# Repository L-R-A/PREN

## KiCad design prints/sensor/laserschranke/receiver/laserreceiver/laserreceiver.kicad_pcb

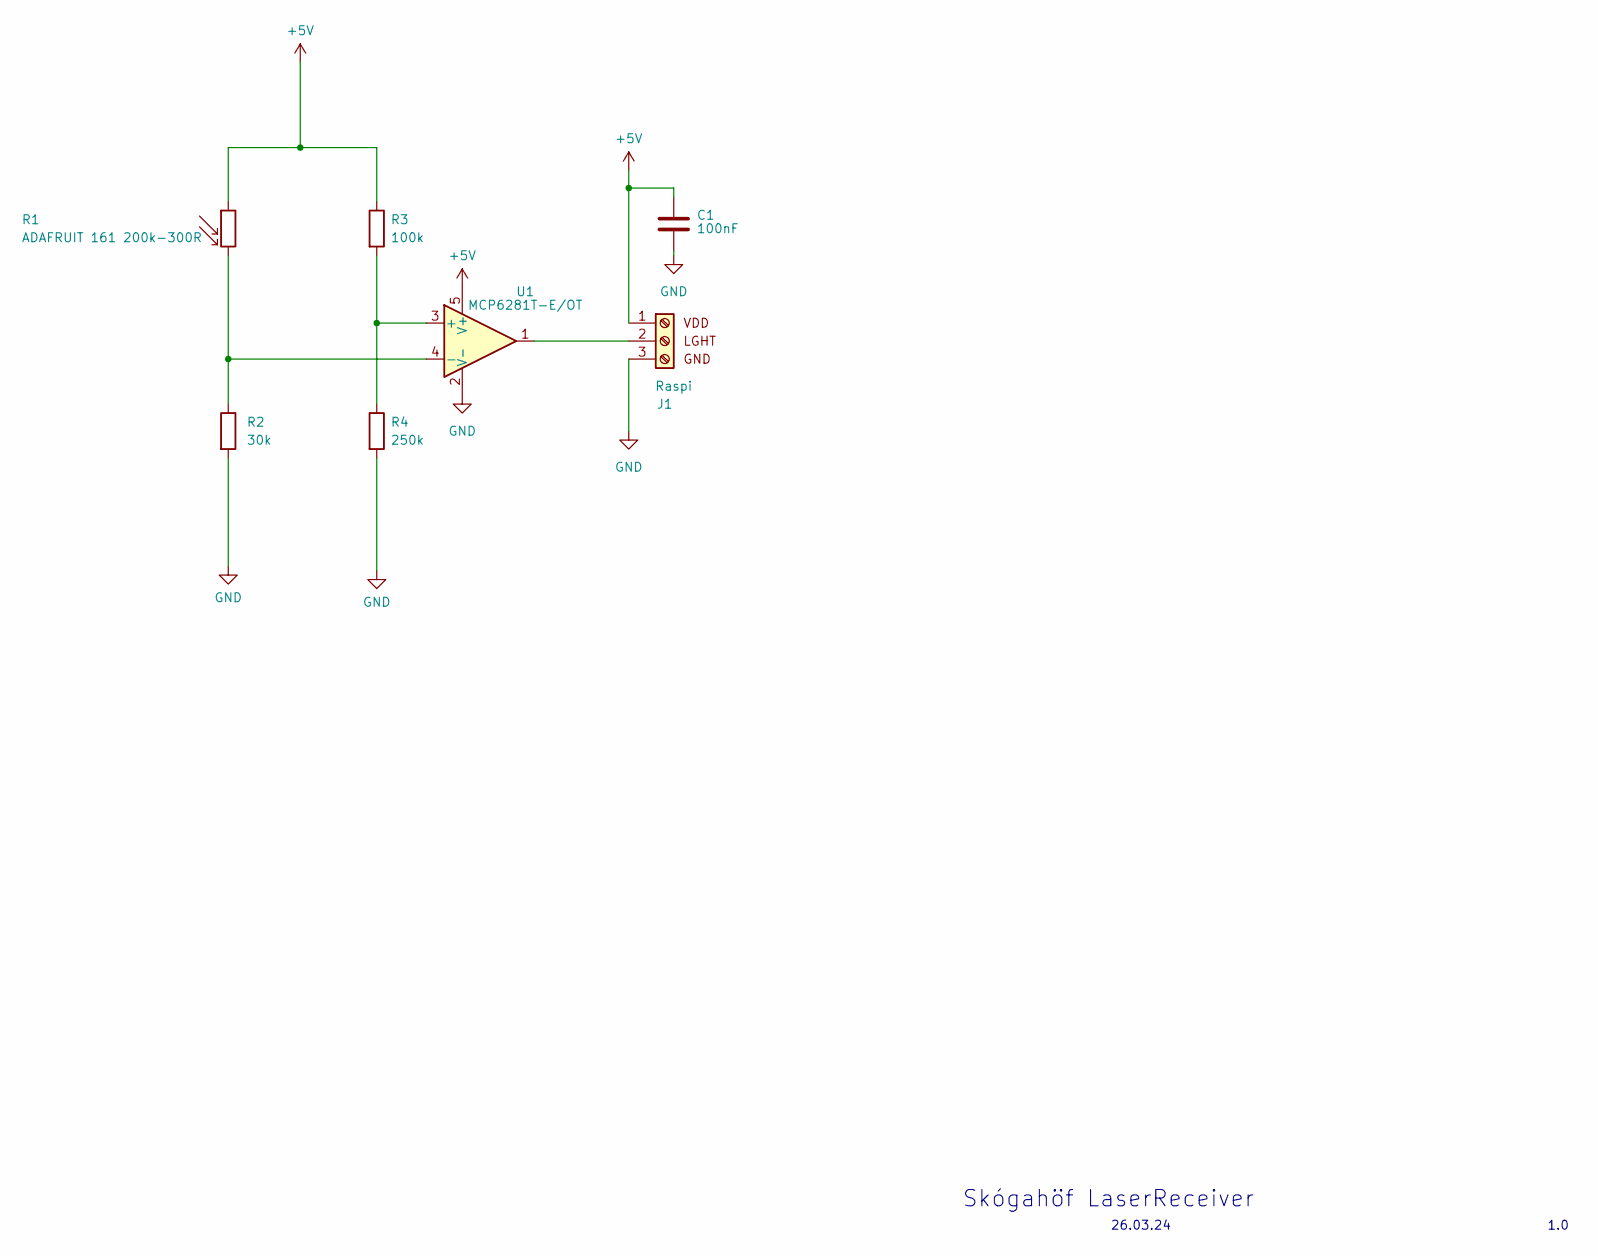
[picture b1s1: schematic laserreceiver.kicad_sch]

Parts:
C1: 100nF; C_0805_2012Metric_Pad1.18x1.45mm_HandSolder
J1: Raspi; TerminalBlock_4Ucon_1x03_P3.50mm_Vertical
R1: ADAFRUIT 161 200k-300R; XDCR_161
R2: 30k; R_0805_2012Metric_Pad1.20x1.40mm_HandSolder
R3: 100k; R_0805_2012Metric_Pad1.20x1.40mm_HandSolder
R4: 250k; R_0805_2012Metric_Pad1.20x1.40mm_HandSolder
U1: MCP6281T-E/OT; SOT-23-5

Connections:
+5V: C1.1, J1.1, R1.1, R3.1, U1.5 (V+)
GND: C1.2, J1.3, R2.2, R4.2, U1.2 (V-)
unnamed: J1.2, U1.1
unnamed: R3.2, R4.1, U1.3 (+)
unnamed: R1.2, R2.1, U1.4 (-)

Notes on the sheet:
1.0
26.03.24
Skógahöf LaserReceiver

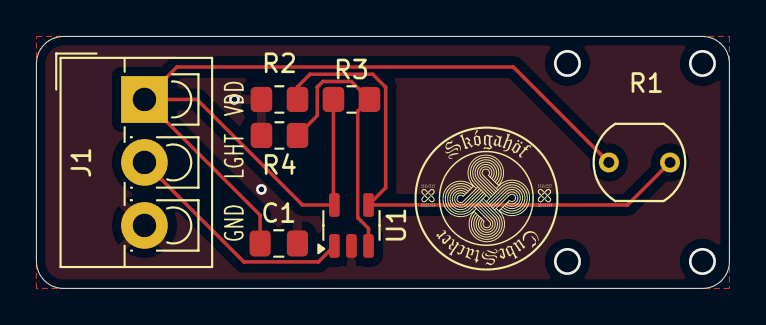
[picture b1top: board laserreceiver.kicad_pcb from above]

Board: 2 copper layers, 38.5 x 14.0 mm, 7 parts (0 on the bottom side), 5 nets.

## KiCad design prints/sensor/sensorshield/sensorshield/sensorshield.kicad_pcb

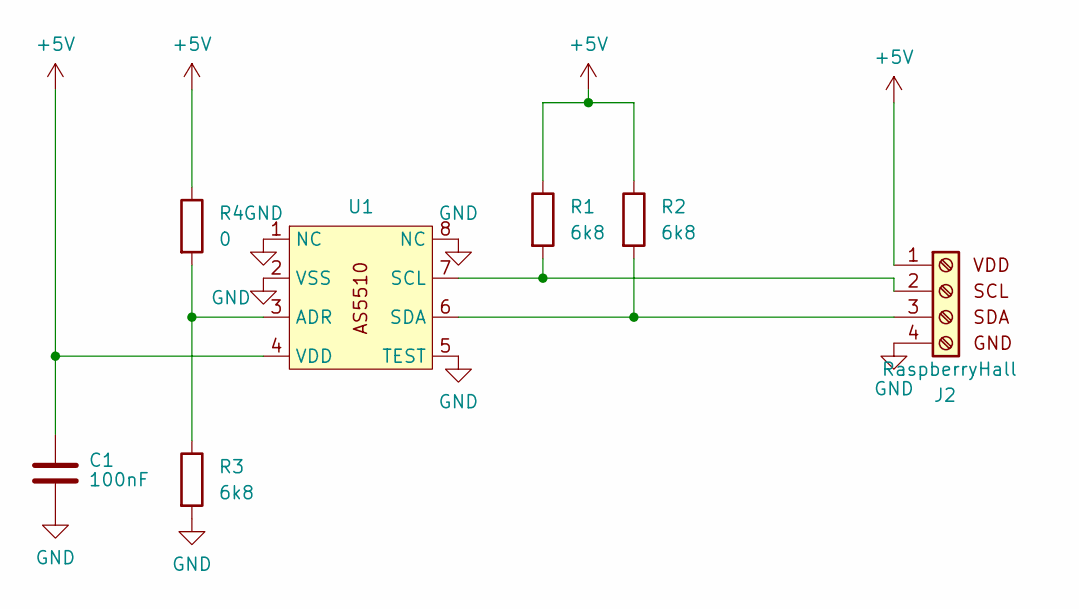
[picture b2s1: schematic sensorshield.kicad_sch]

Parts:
C1: 100nF; C_0805_2012Metric_Pad1.18x1.45mm_HandSolder
J2: RaspberryHall; TerminalBlock_4Ucon_1x04_P3.50mm_Vertical
R1, R2, R3: 6k8; R_0805_2012Metric_Pad1.20x1.40mm_HandSolder
R4: 0; R_0805_2012Metric_Pad1.20x1.40mm_HandSolder
U1: SOIC-8_3.9x4.9mm_P1.27mm

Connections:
+5V: C1.1, J2.1, R1.1, R2.1, R4.1, U1.4 (VDD)
GND: C1.2, J2.4, R3.2, U1.1 (NC), U1.2 (VSS), U1.5 (TEST), U1.8 (NC)
unnamed: J2.2, R1.2, U1.7 (SCL)
unnamed: J2.3, R2.2, U1.6 (SDA)
unnamed: R3.1, R4.2, U1.3 (ADR)

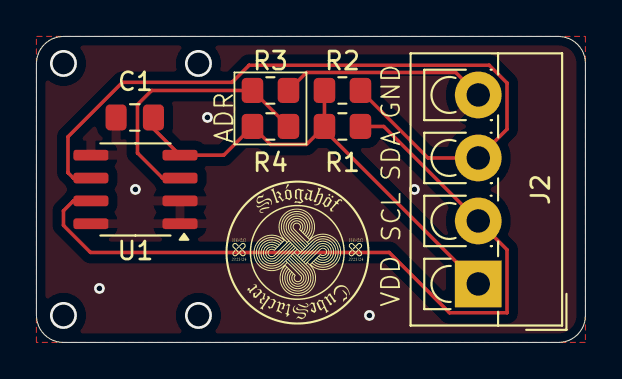
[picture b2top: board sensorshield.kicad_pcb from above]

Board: 2 copper layers, 30.5 x 17.0 mm, 7 parts (0 on the bottom side), 5 nets.

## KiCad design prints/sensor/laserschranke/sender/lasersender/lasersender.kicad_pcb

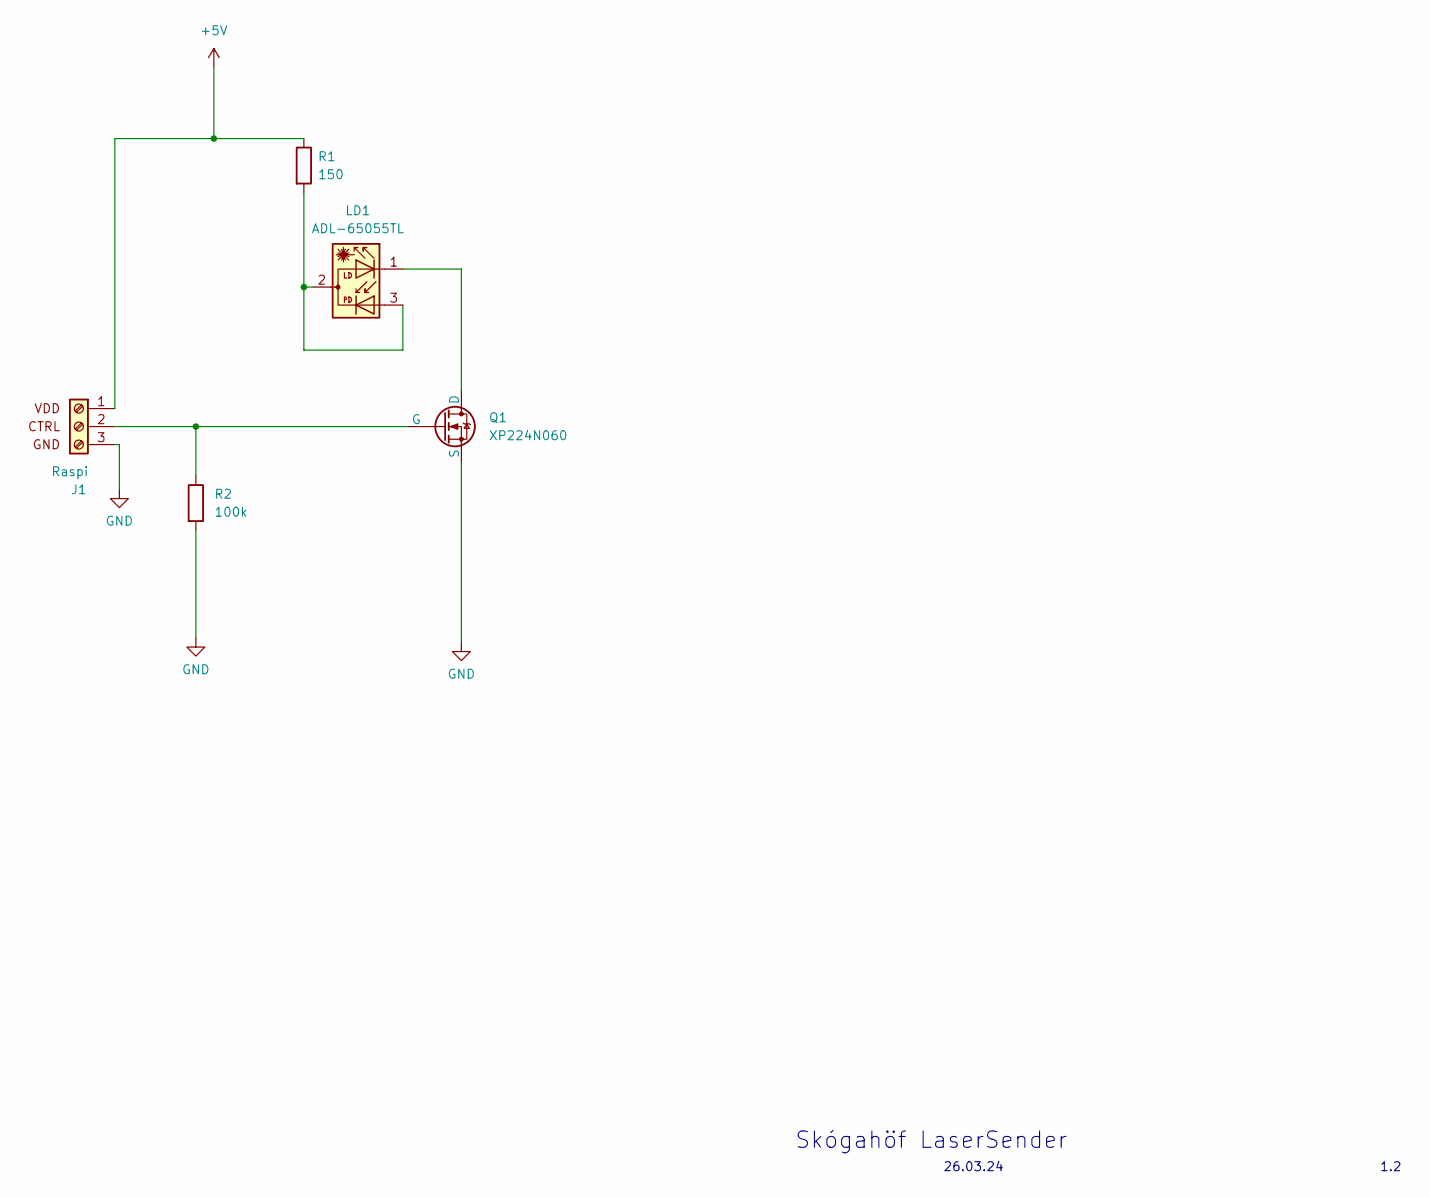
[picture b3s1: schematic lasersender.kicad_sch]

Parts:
J1: Raspi; TerminalBlock_4Ucon_1x03_P3.50mm_Vertical
LD1: ADL-65055TL; LaserDiode_TO56-3
Q1: XP224N060; SOT-323_SC-70
R1: 150; R_0805_2012Metric_Pad1.20x1.40mm_HandSolder
R2: 100k; R_0805_2012Metric_Pad1.20x1.40mm_HandSolder

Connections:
+5V: J1.1, R1.1
GND: J1.3, Q1.3 (S), R2.2
unnamed: J1.2, Q1.2 (G), R2.1
unnamed: LD1.2, LD1.3, R1.2
unnamed: LD1.1, Q1.1 (D)

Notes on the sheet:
26.03.24
Skógahöf LaserSender
1.2

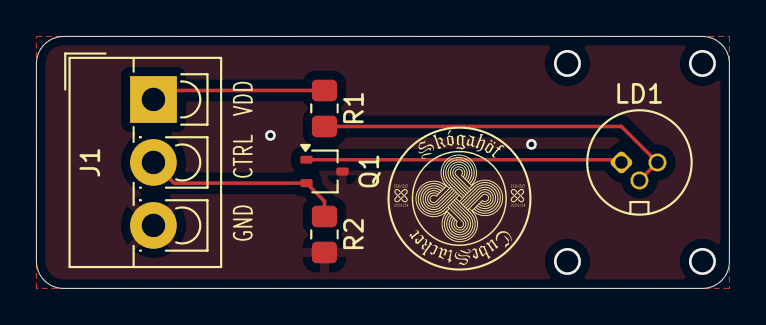
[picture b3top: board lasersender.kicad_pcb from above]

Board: 2 copper layers, 38.5 x 14.0 mm, 5 parts (0 on the bottom side), 5 nets.

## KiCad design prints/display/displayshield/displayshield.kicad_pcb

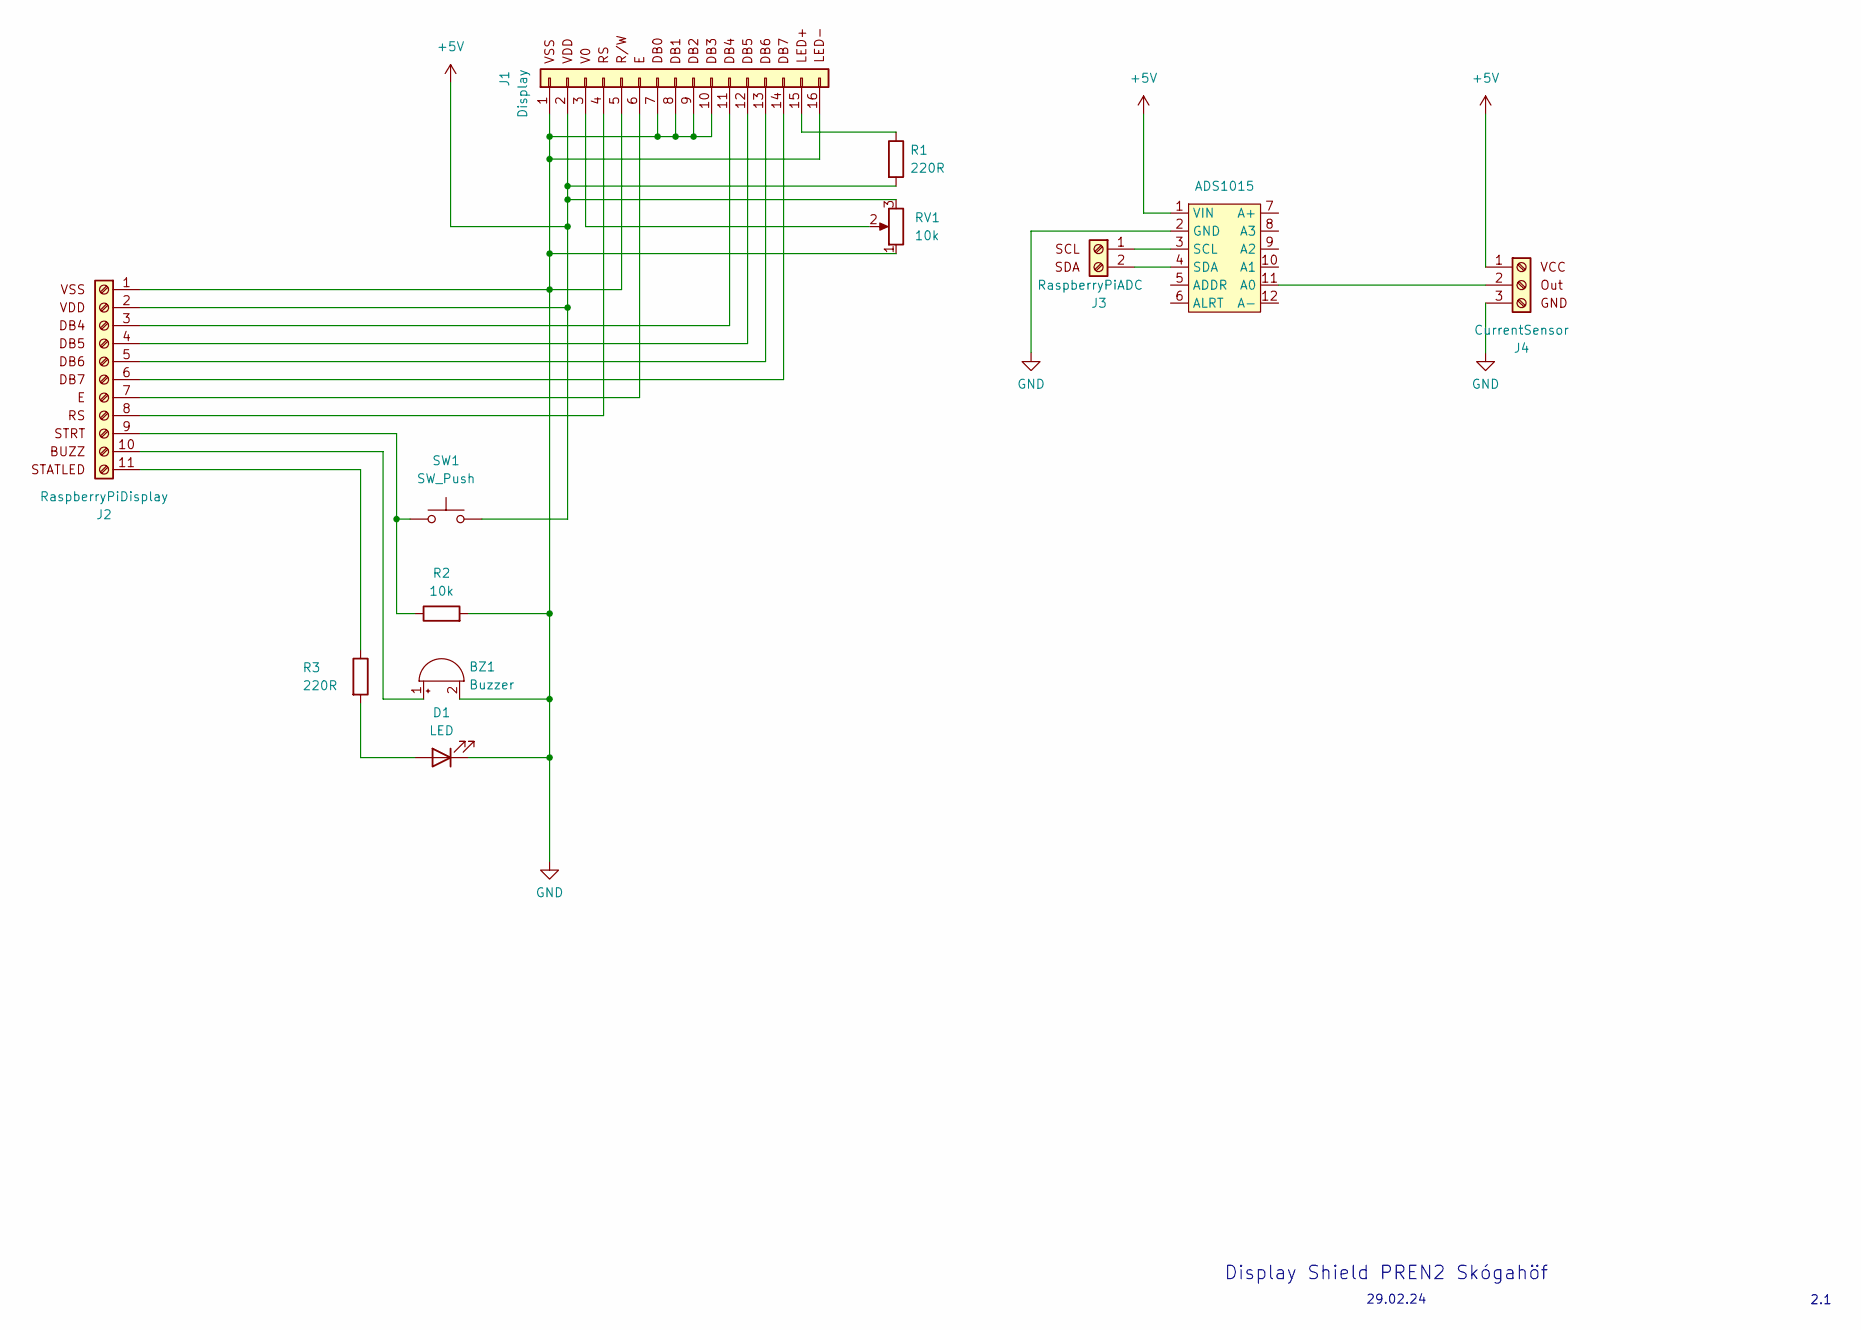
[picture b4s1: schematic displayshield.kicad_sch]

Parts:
ADS1015: ADS1015
BZ1: Buzzer; Buzzer_12x9.5RM7.6
D1: LED; LED_D5.0mm_FlatTop
J1: Display; PinHeader_1x16_P2.54mm_Vertical
J2: RaspberryPiDisplay; TerminalBlock_4Ucon_1x11_P3.50mm_Vertical
J3: RaspberryPiADC; TerminalBlock_4Ucon_1x02_P3.50mm_Vertical
J4: CurrentSensor; TerminalBlock_4Ucon_1x03_P3.50mm_Vertical
R1, R3: 220R; R_0805_2012Metric_Pad1.20x1.40mm_HandSolder
R2: 10k; R_0805_2012Metric_Pad1.20x1.40mm_HandSolder
RV1: 10k; Potentiometer_Bourns_3299W_Vertical
SW1: SW_Push; SW_PUSH_6mm_H8.5mm

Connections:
+5V: ADS1015.1 (VIN), J1.2, J2.2, J4.1, R1.2, RV1.3, SW1.2
GND: ADS1015.2 (GND), BZ1.2 (-), D1.1 (K), J1.1, J1.5, J1.7, J1.8, J1.9, J1.10, J1.16, J2.1, J4.3, R2.2, RV1.1
unnamed: ADS1015.11 (A0), J4.2
unnamed 3: ADS1015.10 (A1); also elsewhere on the board
unnamed 4: ADS1015.9 (A2); also elsewhere on the board
unnamed 5: ADS1015.8 (A3); also elsewhere on the board
unnamed: ADS1015.3 (SCL), J3.1
unnamed: ADS1015.4 (SDA), J3.2
unnamed: BZ1.1 (+), J2.10
unnamed: D1.2 (A), R3.2
unnamed: J1.3, RV1.2
unnamed: J1.4, J2.8
unnamed: J1.6, J2.7
unnamed: J1.11, J2.3
unnamed: J1.12, J2.4
unnamed: J1.13, J2.5
unnamed: J1.14, J2.6
unnamed: J1.15, R1.1
unnamed: J2.9, R2.1, SW1.1
unnamed: J2.11, R3.1

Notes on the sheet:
29.02.24
2.1
Display Shield PREN2 Skógahöf

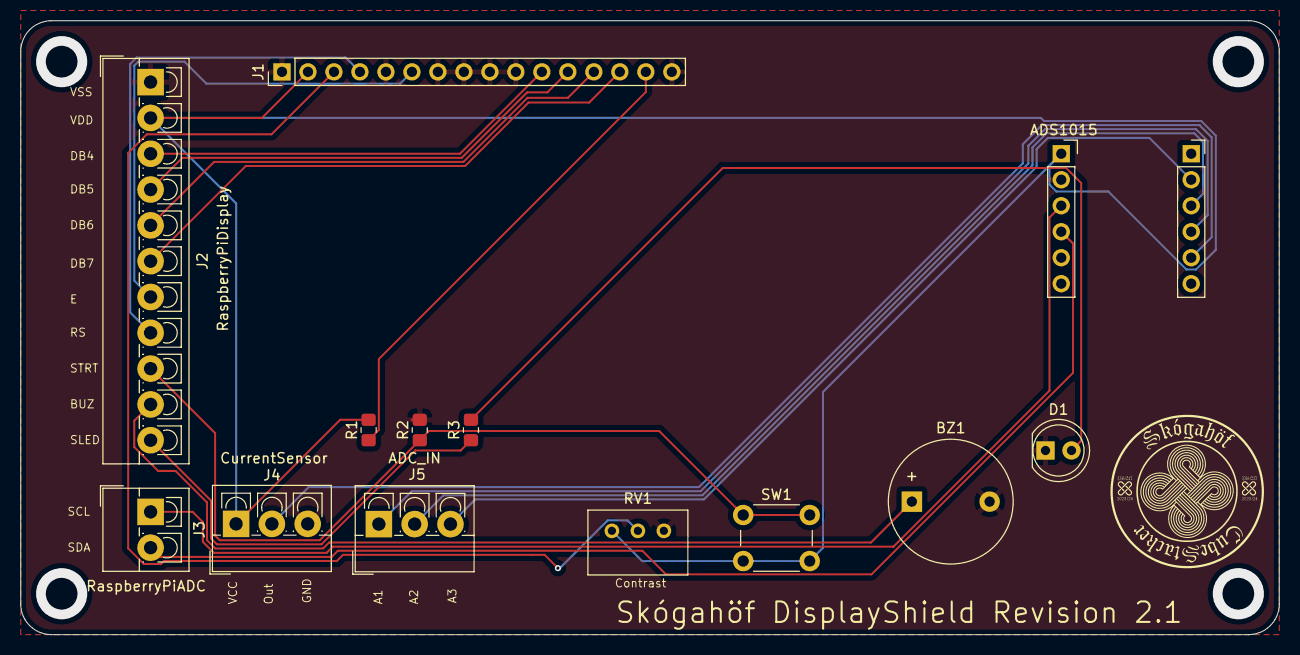
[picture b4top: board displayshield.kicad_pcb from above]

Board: 2 copper layers, 123.0 x 60.0 mm, 13 parts (0 on the bottom side), 20 nets.

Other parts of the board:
J5: ADC_IN; TerminalBlock_4Ucon_1x03_P3.50mm_Vertical

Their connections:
unnamed 3: J5.1; also elsewhere on the board
unnamed 4: J5.2; also elsewhere on the board
unnamed 5: J5.3; also elsewhere on the board

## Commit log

2023-09-22 test commit
2023-10-20 setup structure using python
2023-10-20 add color and contour detection
2023-10-24 some hacking
2023-10-26 cleaned up, added espp folder
2023-10-26 Create PREN_ADC.ino
    added adc
2023-10-26 Update PREN_ADC.ino
    Updated: Gemessener ADC Wert wird anhand Uref in effektiven Spannungswert umgerechnet.
2023-10-26 more hacking
2023-10-27 refactor code
2023-10-27 rename app file
2023-11-02 Update PREN_ADC.ino
    time included, start button included
2023-11-02 refactor use external module
2023-11-03 Update PREN_ADC.ino
    Version 03.11.2023 (Start & Stopp Knopf, Energiemessung, Display)
2023-11-03 add contour stretching
2023-11-03 try out image preprocessing
2023-11-06 update helper class
2023-11-06 try out 3D reconstruction
2023-11-10 update playground
2023-11-15 added servo control
2023-11-22 add scaling factors
2023-11-28 add functinal model training for strategy 2
2023-11-29 make strategy one trainable
2023-12-12 add test data and functions
2023-12-21 add script for testing on raspberry pi
2024-02-23 create demo
2024-02-23 remove unused imports
2024-02-23 a lot of changes
2024-02-29 move machine learning to jupyter
2024-02-29 Added Prints for Displayshield
2024-03-01 Finished Displayshield Print
2024-03-01 3D Prints
2024-03-07 Erstes Testprogram für Motoren-Steuerung
2024-03-07 nützliche Links ergänzt in Kommentaren
2024-03-08 Beide Shields Funktionieren mit diesem Test Code
2024-03-14 add pren lifestream, changes to jupyter script
2024-03-14 fix pixel overwritting
2024-03-14 added new Printfiles for Displayshield and Measurements for second stack
2024-03-14 updated StackMeasurements
2024-03-19 fixed prints
2024-03-19 almost murdered the git repo :( sorry, but fixed now
2024-03-21 adc included
2024-03-21 Created function for getting frame
2024-03-21 add new model, change preprocessing
2024-03-21 updated adc measurement
2024-03-22 random
2024-03-22 start button and endless loop added
2024-03-22 DisplayDriver Included
2024-03-22 Prints for Hallsensor
2024-03-24 add a lot of stuff
2024-03-24 working detection models
2024-03-25 clean up, improve machine learning testing
2024-03-25 added Logininitialisation
2024-03-25 remove unused code
2024-03-25 updated schematics and prints
2024-03-25 added Revision 0.2.1 of Skógahöf Mainschematic
2024-03-26 added Laserbarrier files and calculations
2024-03-26 fixed main schematic :)
2024-03-28 add stuff
2024-03-28 add 10000 data model
2024-04-04 thread angepasst
2024-04-04 added one line
2024-04-04 rewrite lifestream test to write on mem
2024-04-10 added Functioning parts of Steppers
2024-04-10 create raspberry pi module
2024-04-11 meassure time of raspberry script
2024-04-13 add redundancy to videoanalyse
2024-04-13 add redundancy script to raspberry
2024-04-13 fix main.py
2024-04-15 update redundanciy script
2024-04-15 fix stream script error
2024-04-15 fix redundancy algorithm
2024-04-18 Servo Demo added, laser added
2024-04-19 added mainfile for skoga
2024-04-22 changes to Schematics
2024-04-22 move cubedetection to class
2024-04-25 grobes framework
2024-04-25 sandbox and display toying
2024-04-25 edited initialization
2024-04-25 image detection added / init off platform changed
2024-04-25 cube placing edited
2024-05-01 files pre LAGER
2024-05-02 hardcoded demo
2024-05-02 changed threads to process and pigpio to digitalio
2024-05-02 started with Modulisation
2024-05-02 started with Modulisation v2
2024-05-02 schematics update
2024-05-02 edited main, laser, motors and adc
2024-05-08 add 98-99% cube detection model
2024-05-10 added more Displaystuff
2024-05-10 Raspi
2024-05-10 fixed procedure of main
2024-05-10 strings
2024-05-18 speed up redundancy check
2024-05-23 update ai model
2024-05-24 added stupid shit
2024-06-15 add file for rest api requests
2024-06-19 add auth token, fix not working requests
2024-06-28 Updated code on raspberry
2024-07-03 tuning
2024-07-03 all my homies hate the sun
2024-07-03 besser gahts
